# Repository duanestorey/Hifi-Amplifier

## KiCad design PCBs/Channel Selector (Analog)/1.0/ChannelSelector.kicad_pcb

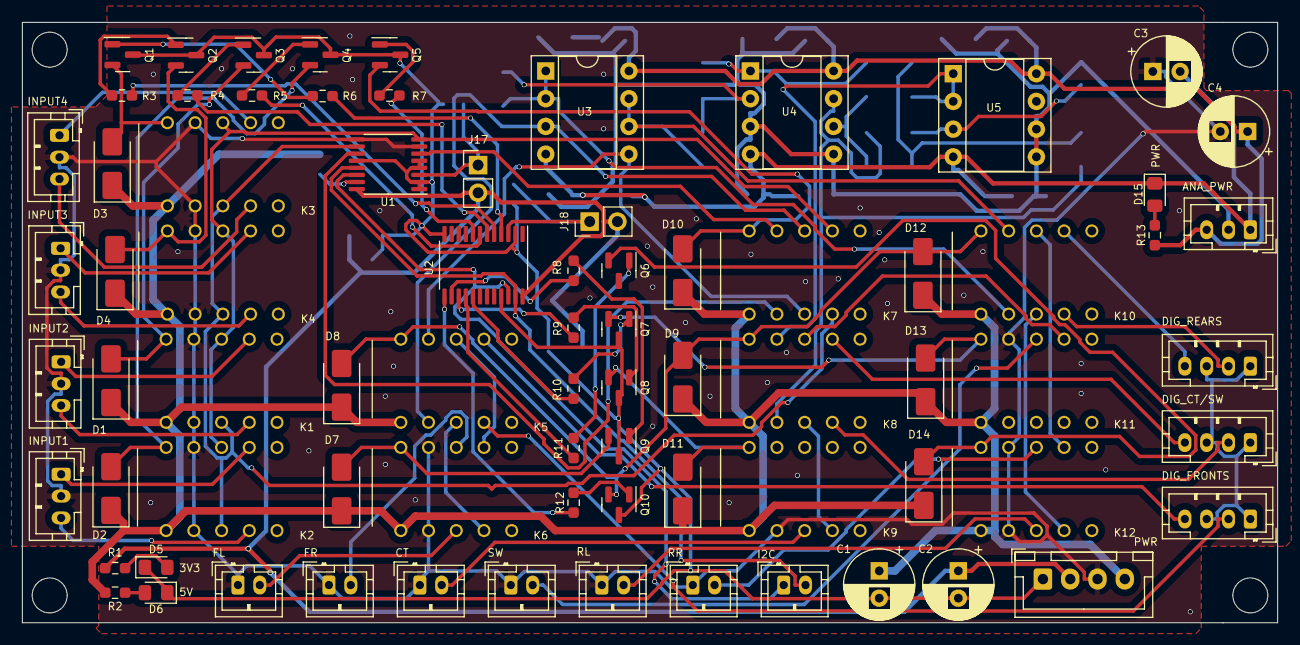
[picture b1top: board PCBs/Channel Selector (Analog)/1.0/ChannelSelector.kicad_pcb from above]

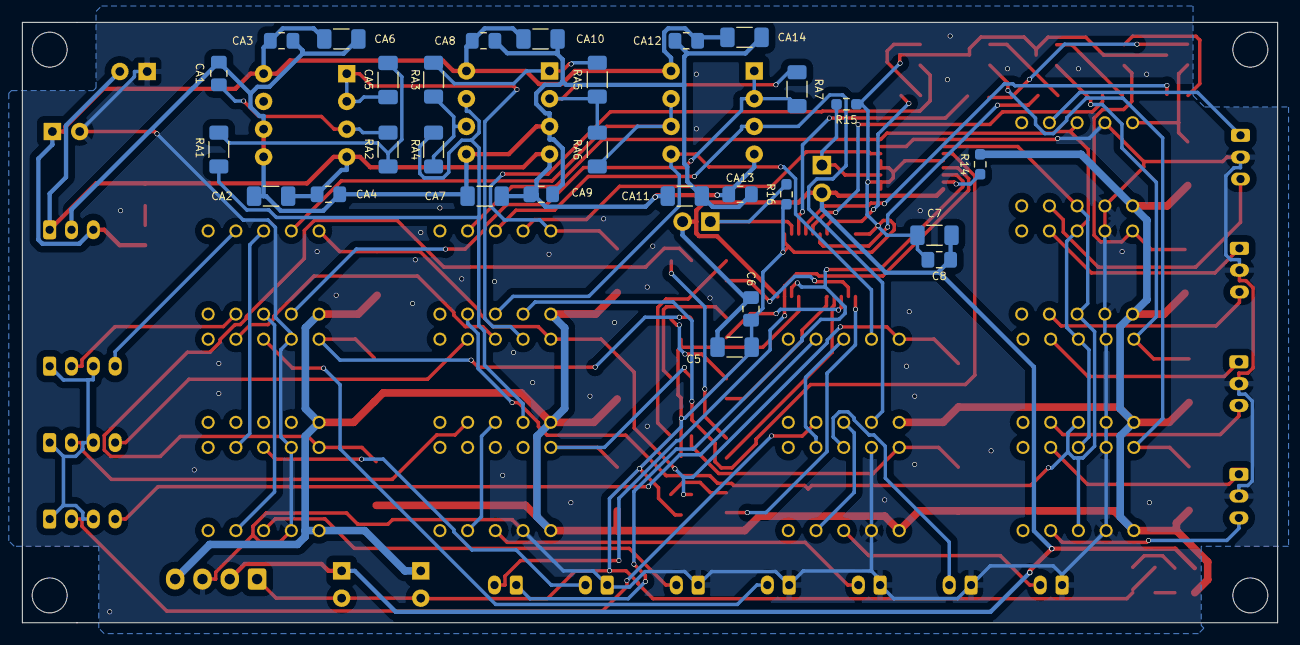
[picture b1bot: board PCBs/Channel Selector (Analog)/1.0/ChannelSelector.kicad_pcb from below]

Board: 2 copper layers, 115.0 x 55.0 mm, 109 parts (28 on the bottom side), 87 nets.

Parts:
C1, C2, C3, C4: 100u; CP_Radial_D6.3mm_P2.50mm
C5, C7: 10U; C_1206_3216Metric_Pad1.33x1.80mm_HandSolder
C6, C8: 0.1U; C_0805_2012Metric_Pad1.18x1.45mm_HandSolder
CA1: 10n; C_0805_2012Metric_Pad1.18x1.45mm_HandSolder
CA2, CA6, CA7, CA10, CA11, CA14: 10u; C_1206_3216Metric_Pad1.33x1.80mm_HandSolder
CA3, CA4, CA8, CA9, CA12, CA13: 0.1u; C_0805_2012Metric_Pad1.18x1.45mm_HandSolder
CA5: 100n; C_1206_3216Metric_Pad1.33x1.80mm_HandSolder
D1, D2, D3, D4, D7, D8, D9, D10, D11, D12, D13, D14: 1N4001; D_SMA
D5: YELLOW; LED_0805_2012Metric_Pad1.15x1.40mm_HandSolder
D6: BLUE; LED_0805_2012Metric_Pad1.15x1.40mm_HandSolder
D15: WHITE; LED_0805_2012Metric_Pad1.15x1.40mm_HandSolder
H1, H2, H3, H4: MountingHole; MountingHole_3.2mm_M3
J1, J2, J3, J4, J16: Conn_01x03_Pin; JST_PH_B3B-PH-K_1x03_P2.00mm_Vertical
J5, J6, J7, J8, J9, J10: Conn_01x02_Pin; JST_PH_B2B-PH-K_1x02_P2.00mm_Vertical
J11: Conn_01x02_Male; JST_PH_B2B-PH-K_1x02_P2.00mm_Vertical
J12: Conn_01x04_Pin; JST_XH_B4B-XH-A_1x04_P2.50mm_Vertical
J13, J14, J15: Conn_01x04_Pin; JST_PH_B4B-PH-K_1x04_P2.00mm_Vertical
J17, J18: Conn_01x02_Pin; PinHeader_1x02_P2.54mm_Vertical
K1, K3, K4, K5, K6, K7, K8, K9, K10, K11, K12: EC2-5NU; KEMET EA2
K2: KEMET; KEMET EA2
Q1, Q2, Q3, Q4, Q5, Q6, Q7, Q8, Q9, Q10: BC859; SOT-23
R1: 430R; R_0603_1608Metric_Pad0.98x0.95mm_HandSolder
R2, R15, R16: 670R; R_0603_1608Metric_Pad0.98x0.95mm_HandSolder
R3, R4, R5, R6, R7, R8, R9, R10, R11, R12: 1K; R_0603_1608Metric_Pad0.98x0.95mm_HandSolder
R13: 5K; R_0603_1608Metric_Pad0.98x0.95mm_HandSolder
R14: 0R; R_0603_1608Metric_Pad0.98x0.95mm_HandSolder
RA1: 7.5K; R_1206_3216Metric_Pad1.30x1.75mm_HandSolder
RA2: 130K; R_1206_3216Metric_Pad1.30x1.75mm_HandSolder
RA3, RA4, RA5: 1K; R_1206_3216Metric_Pad1.30x1.75mm_HandSolder
RA6, RA7: 2K; R_1206_3216Metric_Pad1.30x1.75mm_HandSolder
U1: DS1881; TSSOP-16_4.4x5mm_P0.65mm
U2: TCA9555; TSSOP-24_4.4x7.8mm_P0.65mm
U3, U4, U5: OPA2134; DIP-8_W7.62mm_Socket

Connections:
3V3: C2.1, C5.1, C6.1, C7.1, C8.1, J12.2, J17.2, J18.2, R1.1, U1.16 (VDD), U2.24 (VDD)
5CHGND: J13.1, J13.3, J14.1, J14.3, J15.1, J15.3
5V: C1.1, D1.1 (K), D2.1 (K), D3.1 (K), D4.1 (K), D7.1 (K), D8.1 (K), D9.1 (K), D10.1 (K), D11.1 (K), D12.1 (K), D13.1 (K), D14.1 (K), J12.4, K1.1, K2.1, K3.1, K4.1, K5.1, K6.1, K7.1, K8.1, K9.1, K10.1, K11.1, K12.1, R2.1, R14.2
AGND: C3.1, C4.2, J1.2, J2.2, J3.2, J4.2, J5.1, J6.1, J7.1, J8.1, J9.1, J10.1, J12.3, K1.3, K1.10, K2.3, K2.10, K3.3, K3.10, K4.3, K4.10, K6.3, K6.10, K9.3, K11.10, K12.3, K12.10, U1.7 (L0), U1.9 (L1)
CT: J7.2, K9.4
CT_A: K8.3, RA1.1, RA4.1, U4.7 (OutB)
CT_DIG: J14.2, K8.5
CT_EN: R9.1, U2.15 (IO1_2)
CT_SIG: K8.4, K9.5
DIGCTL: R12.1, U2.13 (IO1_0)
FL: J5.2, K6.4
FL_A: K5.3, K7.9, U3.3 (InA+)
FL_AIN: K1.9, K2.9, K3.9, K4.9, K7.8, U1.8 (H0)
FL_AV: K7.10, U1.6 (W0)
FL_DIG: J15.2, K5.5
FL_SIG: K5.4, K6.5
FR: J6.2, K6.9
FRONT_EN: R8.1, U2.14 (IO1_1)
FR_A: K5.10, K7.4, U3.5 (InB+)
FR_AIN: K1.4, K2.4, K3.4, K4.4, K7.5, U1.10 (H1)
FR_AV: K7.3, U1.11 (W1)
FR_DIG: J15.4, K5.8
FR_SIG: K5.9, K6.8
GND: C1.2, C2.2, C5.2, C6.2, C7.2, C8.2, D5.1 (K), D6.1 (K), J12.1, Q1.3 (C), Q2.3 (C), Q3.3 (C), Q4.3 (C), Q5.3 (C), Q7.3 (C), Q8.3 (C), Q9.3 (C), Q10.3 (C), R15.1, R16.1, U1.1 (GND), U1.2 (A2), U1.4 (V-), U1.5 (A0), U1.12 (~CE), U2.2 (A1), U2.12 (VSS), U2.21 (A0)
GPIO_A2: J18.1, R16.2, U2.3 (A2)
unnamed: CA5.2, RA1.2, RA2.1
unnamed: D1.2 (A), K1.12, Q3.2 (E)
unnamed: D2.2 (A), K2.12, Q4.2 (E)
unnamed: D3.2 (A), K3.12, Q1.2 (E)
unnamed: D4.2 (A), K4.12, Q2.2 (E)
unnamed: D5.2 (A), R1.2
unnamed: D6.2 (A), R2.2
unnamed: D7.2 (A), K6.12, Q9.2 (E)
unnamed: D10.2 (A), K7.12, Q5.2 (E)
unnamed: D11.2 (A), K9.12, Q8.2 (E)
unnamed: D8.2 (A), D9.2 (A), D12.2 (A), K5.12, K8.12, K10.12, Q10.2 (E)
unnamed: D13.2 (A), K11.12, Q7.2 (E)
unnamed: D14.2 (A), K12.12, Q6.2 (E)
unnamed: D15.2 (A), R13.2
unnamed: Q1.1 (B), R6.2
unnamed: Q2.1 (B), R3.2
unnamed: Q3.1 (B), R4.2
unnamed: Q4.1 (B), R5.2
unnamed: Q5.1 (B), R7.2
unnamed: Q6.1 (B), R11.2
unnamed: Q7.1 (B), R10.2
unnamed: Q8.1 (B), R9.2
unnamed: Q9.1 (B), R8.2
unnamed: Q10.1 (B), R12.2
unnamed: R14.1, U1.15 (VCC)
unnamed: RA5.1, RA6.2, RA7.2, U4.2 (InA-)
unnamed: RA3.1, RA4.2, U4.6 (InB-)
unnamed: RA3.2, RA5.2, U4.1 (OutA)
unnamed: CA1.2, RA2.2, U5.3 (InA+)
OPGND: CA1.1, CA2.1, CA3.1, CA4.1, CA6.1, CA7.1, CA8.1, CA9.1, CA10.1, CA11.1, CA12.1, CA13.1, CA14.1, J16.2, U4.3 (InA+), U4.5 (InB+), U5.5 (InB+), U5.6 (InB-)
POT_A1: J17.1, R15.2, U1.3 (A1)
RCA1: R5.1, U2.7 (IO0_3)
RCA1_L: J4.1, K2.8
RCA1_R: J4.3, K2.5
RCA2: R4.1, U2.6 (IO0_2)
RCA2_L: J3.1, K1.8
RCA2_R: J3.3, K1.5
RCA3: R3.1, U2.5 (IO0_1)
RCA3_L: J2.1, K4.8
RCA3_R: J2.3, K4.5
RCA4: R6.1, U2.4 (IO0_0)
RCA4_L: J1.1, K3.8
RCA4_R: J1.3, K3.5
REARS_EN: R11.1, U2.16 (IO1_3)
RL: J9.2, K12.4
RL_A: K10.3, RA7.1, U3.1 (OutA), U3.2 (InA-)
RL_DIG: J13.2, K10.5
RL_SIG: K10.4, K12.5
RR: J10.2, K12.9
RR_A: K10.10, RA6.1, U3.6 (InB-), U3.7 (OutB)
RR_DIG: J13.4, K10.8
RR_SIG: K10.9, K12.8
SCL: J11.1, U1.14 (SCL), U2.22 (SCL)
SDA: J11.2, U1.13 (SDA), U2.23 (SDA)
SW: J8.2, K11.9
SW_A: CA5.1, K8.10, U5.1 (OutA), U5.2 (InA-)
SW_DIG: J14.4, K8.8
SW_EN: R10.1, U2.17 (IO1_4)
SW_SIG: K8.9, K11.8
V+: C4.1, CA3.2, CA6.2, CA8.2, CA10.2, CA12.2, CA14.2, J16.3, R13.1, U3.8 (V+), U4.8 (V+), U5.8 (V+)
V-: C3.2, CA2.2, CA4.2, CA7.2, CA9.2, CA11.2, CA13.2, D15.1 (K), J16.1, U3.4 (V-), U4.4 (V-), U5.4 (V-)
VOLCTL: R7.1, U2.8 (IO0_4)

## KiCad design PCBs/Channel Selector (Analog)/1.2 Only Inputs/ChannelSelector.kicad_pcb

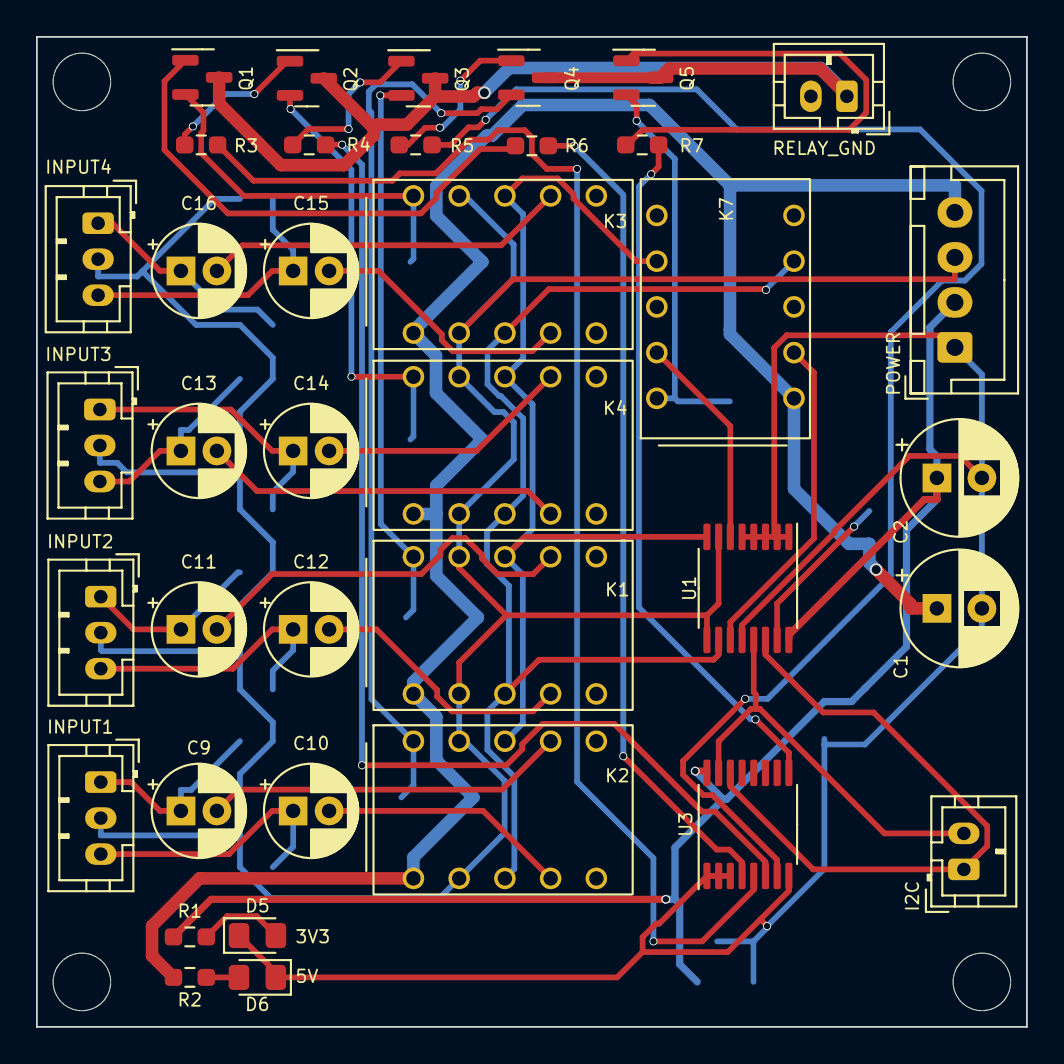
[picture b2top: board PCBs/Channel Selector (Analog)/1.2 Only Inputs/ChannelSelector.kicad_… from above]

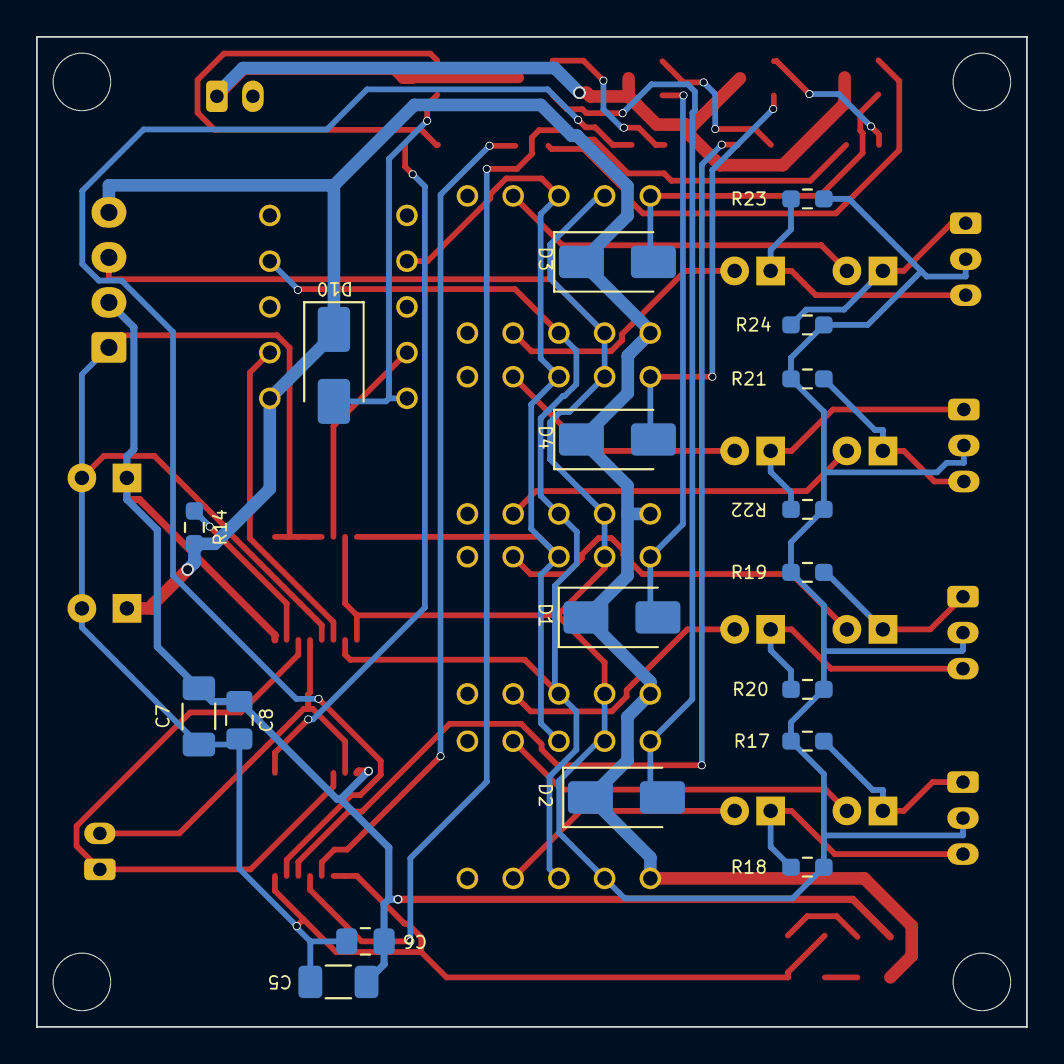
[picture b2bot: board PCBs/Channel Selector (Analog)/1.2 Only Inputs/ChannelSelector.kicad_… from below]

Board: 2 copper layers, 55.0 x 55.0 mm, 60 parts (18 on the bottom side), 45 nets.

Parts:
C1, C2: 100u; CP_Radial_D6.3mm_P2.50mm
C5, C7: 10U; C_1206_3216Metric_Pad1.33x1.80mm_HandSolder
C6, C8: 0.1U; C_0805_2012Metric_Pad1.18x1.45mm_HandSolder
C9, C10, C11, C12, C13, C14, C15, C16: 10u; CP_Radial_D5.0mm_P2.00mm
D1, D2, D3, D4, D10: 1N4001; D_SMA
D5: YELLOW; LED_0805_2012Metric_Pad1.15x1.40mm_HandSolder
D6: BLUE; LED_0805_2012Metric_Pad1.15x1.40mm_HandSolder
H1, H2, H3, H4: MountingHole; MountingHole_3.2mm_M3
J1, J2, J3, J4: Conn_01x03_Pin; JST_PH_B3B-PH-K_1x03_P2.00mm_Vertical
J11: Conn_01x02_Male; JST_PH_B2B-PH-K_1x02_P2.00mm_Vertical
J12: Conn_01x04_Pin; JST_XH_B4B-XH-A_1x04_P2.50mm_Vertical
J19: Conn_01x02_Pin; JST_PH_B2B-PH-K_1x02_P2.00mm_Vertical
K1, K3, K4, K7: EC2-5NU; KEMET EA2
K2: KEMET; KEMET EA2
Q1, Q2, Q3, Q4, Q5: BC859; SOT-23
R1: 430R; R_0603_1608Metric_Pad0.98x0.95mm_HandSolder
R2: 670R; R_0603_1608Metric_Pad0.98x0.95mm_HandSolder
R3, R4, R5, R6, R7: 1K; R_0603_1608Metric_Pad0.98x0.95mm_HandSolder
R14: 0R; R_0603_1608Metric_Pad0.98x0.95mm_HandSolder
R17, R18, R19, R20, R21, R22, R23, R24: 10K; R_0603_1608Metric_Pad0.98x0.95mm_HandSolder
U1: DS1881; TSSOP-16_4.4x5mm_P0.65mm
U3: TCA9554PW; TSSOP-16_4.4x5mm_P0.65mm

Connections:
3V3: C2.1, C5.1, C6.1, C7.1, C8.1, J12.2, R1.1, U1.16 (VDD), U3.16 (VDD)
5V: C1.1, D1.1 (K), D2.1 (K), D3.1 (K), D4.1 (K), D10.1 (K), J12.4, K1.1, K2.1, K3.1, K4.1, K7.1, R2.1, R14.2
AGND: J1.2, J2.2, J3.2, J4.2, J12.3, K1.3, K1.10, K2.3, K2.10, K3.3, K3.10, K4.3, K4.10, R17.1, R18.1, R19.1, R20.1, R21.1, R22.1, R23.1, R24.1, U1.7 (L0), U1.9 (L1)
FL_AIN: K1.9, K2.9, K3.9, K4.9, K7.8, U1.8 (H0)
FL_AV: K7.10, U1.6 (W0)
FR_AIN: K1.4, K2.4, K3.4, K4.4, K7.5, U1.10 (H1)
FR_AV: K7.3, U1.11 (W1)
GND: C1.2, C2.2, C5.2, C6.2, C7.2, C8.2, D5.1 (K), D6.1 (K), J12.1, U1.1 (GND), U1.2 (A2), U1.3 (A1), U1.4 (V-), U1.5 (A0), U1.12 (~CE), U3.1 (A0), U3.2 (A1), U3.3 (A2), U3.8 (GND)
unnamed: D1.2 (A), K1.12, Q3.2 (E)
unnamed: D2.2 (A), K2.12, Q4.2 (E)
unnamed: D3.2 (A), K3.12, Q1.2 (E)
unnamed: D4.2 (A), K4.12, Q2.2 (E)
unnamed: D5.2 (A), R1.2
unnamed: D6.2 (A), R2.2
unnamed: D10.2 (A), K7.12, Q5.2 (E)
unnamed: C16.1, J1.1, R24.2
unnamed: C15.1, J1.3, R23.2
unnamed: C14.1, J2.1, R22.2
unnamed: C13.1, J2.3, R21.2
unnamed: C11.1, J3.1, R19.2
unnamed: C12.1, J3.3, R20.2
unnamed: C9.1, J4.1, R17.2
unnamed: C10.1, J4.3, R18.2
unnamed: Q1.1 (B), R6.2
unnamed: Q2.1 (B), R3.2
unnamed: Q3.1 (B), R4.2
unnamed: Q4.1 (B), R5.2
unnamed: Q5.1 (B), R7.2
unnamed: R14.1, U1.15 (VCC)
PGND: J19.1, Q1.3 (C), Q2.3 (C), Q3.3 (C), Q4.3 (C), Q5.3 (C)
RCA1: R5.1, U3.7 (P3)
RCA1_L: C9.2, K2.8
RCA1_R: C10.2, K2.5
RCA2: R4.1, U3.6 (P2)
RCA2_L: C11.2, K1.8
RCA2_R: C12.2, K1.5
RCA3: R3.1, U3.5 (P1)
RCA3_L: C14.2, K4.8
RCA3_R: C13.2, K4.5
RCA4: R6.1, U3.4 (P0)
RCA4_L: C16.2, K3.8
RCA4_R: C15.2, K3.5
SCL: J11.1, U1.14 (SCL), U3.14 (SCL)
SDA: J11.2, U1.13 (SDA), U3.15 (SDA)
VOLCTL: R7.1, U3.9 (P4)

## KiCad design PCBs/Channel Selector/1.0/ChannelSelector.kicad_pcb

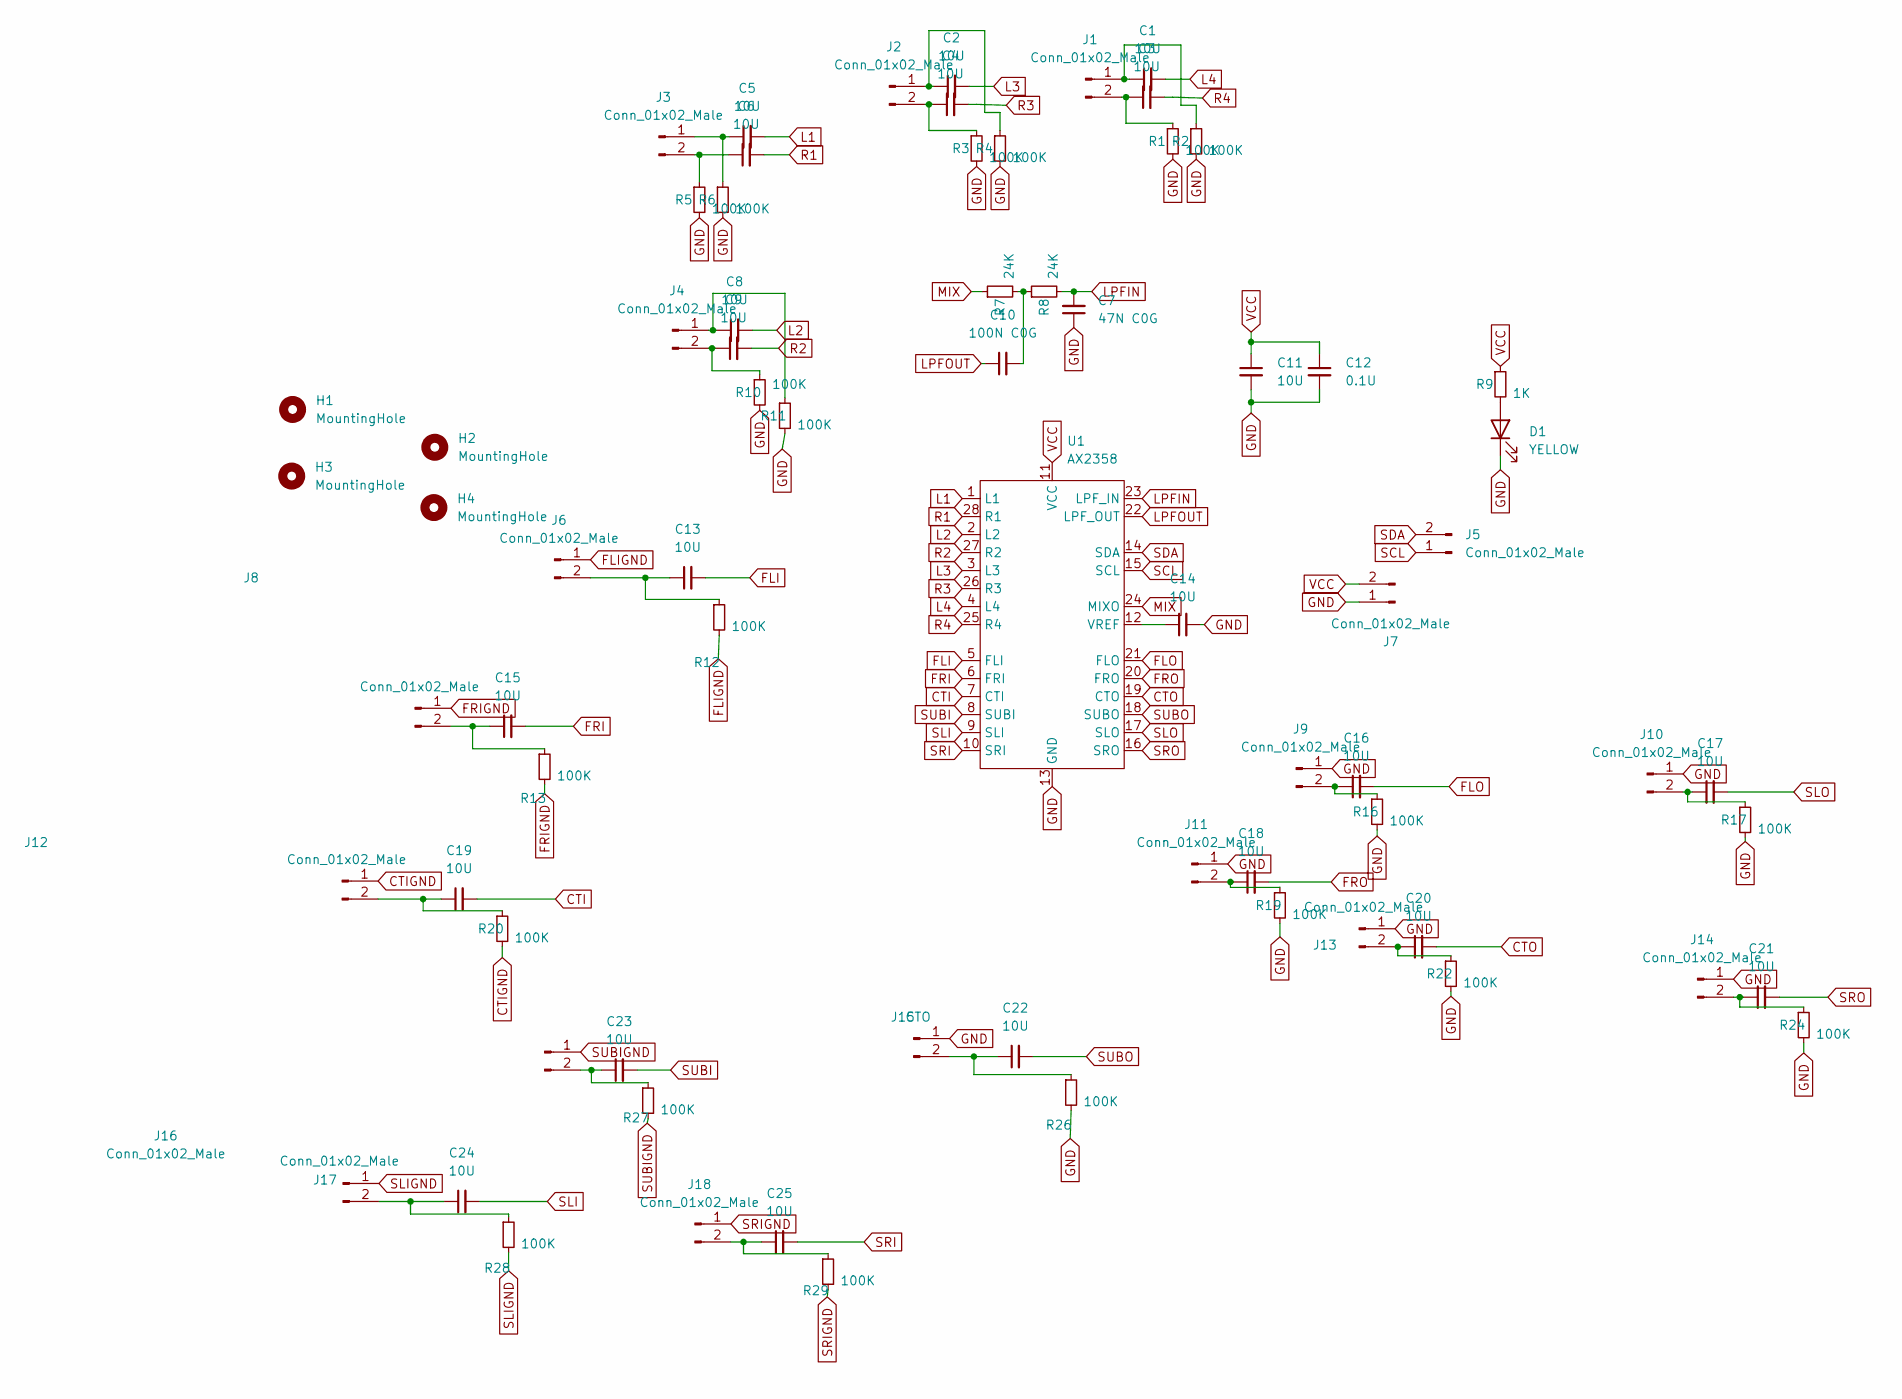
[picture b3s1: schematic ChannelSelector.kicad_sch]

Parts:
C1, C2, C3, C4, C5, C6, C8, C9, C13, C15, C16, C17, C18, C19, C20, C21, C22, C23, C24, C25: 10U; CP_Radial_D5.0mm_P2.50mm
C7: 47N C0G; C_1206_3216Metric_Pad1.33x1.80mm_HandSolder
C10: 100N C0G; C_1206_3216Metric_Pad1.33x1.80mm_HandSolder
C11, C14: 10U; C_1206_3216Metric_Pad1.33x1.80mm_HandSolder
C12: 0.1U; C_0805_2012Metric_Pad1.18x1.45mm_HandSolder
D1: YELLOW; LED_0805_2012Metric_Pad1.15x1.40mm_HandSolder
H1, H2, H3, H4: MountingHole; MountingHole_3.2mm_M3
J1, J2, J3, J4, J5, J6, J7, J8, J9, J10, J11, J12, J13, J14, J16, J17, J18: Conn_01x02_Male; JST_PH_B2B-PH-K_1x02_P2.00mm_Vertical
J15: CTO; JST_PH_B2B-PH-K_1x02_P2.00mm_Vertical
R1, R2, R3, R4, R5, R6, R10, R11, R12, R13, R16, R17, R19, R20, R22, R24, R26, R27, R28, R29: 100K; R_0805_2012Metric_Pad1.20x1.40mm_HandSolder
R7, R8: 24K; R_0805_2012Metric_Pad1.20x1.40mm_HandSolder
R9: 1K; R_0603_1608Metric_Pad0.98x0.95mm_HandSolder
U1: AX2358; SOIC-28W_7.5x18.7mm_P1.27mm

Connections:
CTI: C19.2, U1.7 (CTI)
CTIGND: J12.1, R20.2
CTO: C20.2, U1.19 (CTO)
FLI: C13.2, U1.5 (FLI)
FLIGND: J6.1, R12.2
FLO: C16.2, U1.21 (FLO)
FRI: C15.2, U1.6 (FRI)
FRIGND: J8.1, R13.2
FRO: C18.2, U1.20 (FRO)
GND: C7.1, C11.2, C12.2, C14.2, D1.1 (K), J7.1, J9.1, J10.1, J11.1, J13.1, J14.1, J15.1, R1.2, R2.2, R3.2, R4.2, R5.2, R6.2, R10.2, R11.2, R16.2, R17.2, R19.2, R22.2, R24.2, R26.2, U1.13 (GND)
L1: C5.2, U1.1 (L1)
L2: C8.2, U1.2 (L2)
L3: C2.2, U1.3 (L3)
L4: C1.2, U1.4 (L4)
LPFIN: C7.2, R8.2, U1.23 (LPF_IN)
LPFOUT: C10.1, U1.22 (LPF_OUT)
MIX: R7.1, U1.24 (MIXO)
unnamed: C10.2, R7.2, R8.1
unnamed: D1.2 (A), R9.2
unnamed: C1.1, J1.1, R2.1
unnamed: C3.1, J1.2, R1.1
unnamed: C2.1, J2.1, R4.1
unnamed: C4.1, J2.2, R3.1
unnamed: C5.1, J3.1, R6.1
unnamed: C6.1, J3.2, R5.1
unnamed: C8.1, J4.1, R11.1
unnamed: C9.1, J4.2, R10.1
unnamed: C13.1, J6.2, R12.1
unnamed: C15.1, J8.2, R13.1
unnamed: C16.1, J9.2, R16.1
unnamed: C17.1, J10.2, R17.1
unnamed: C18.1, J11.2, R19.1
unnamed: C19.1, J12.2, R20.1
unnamed: C20.1, J13.2, R22.1
unnamed: C21.1, J14.2, R24.1
unnamed: C22.1, J15.2, R26.1
unnamed: C23.1, J16.2, R27.1
unnamed: C24.1, J17.2, R28.1
unnamed: C25.1, J18.2, R29.1
unnamed: C14.1, U1.12 (VREF)
R1: C6.2, U1.28 (R1)
R2: C9.2, U1.27 (R2)
R3: C4.2, U1.26 (R3)
R4: C3.2, U1.25 (R4)
SCL: J5.1, U1.15 (SCL)
SDA: J5.2, U1.14 (SDA)
SLI: C24.2, U1.9 (SLI)
SLIGND: J17.1, R28.2
SLO: C17.2, U1.17 (SLO)
SRI: C25.2, U1.10 (SRI)
SRIGND: J18.1, R29.2
SRO: C21.2, U1.16 (SRO)
SUBI: C23.2, U1.8 (SUBI)
SUBIGND: J16.1, R27.2
SUBO: C22.2, U1.18 (SUBO)
VCC: C11.1, C12.1, J7.2, R9.1, U1.11 (VCC)

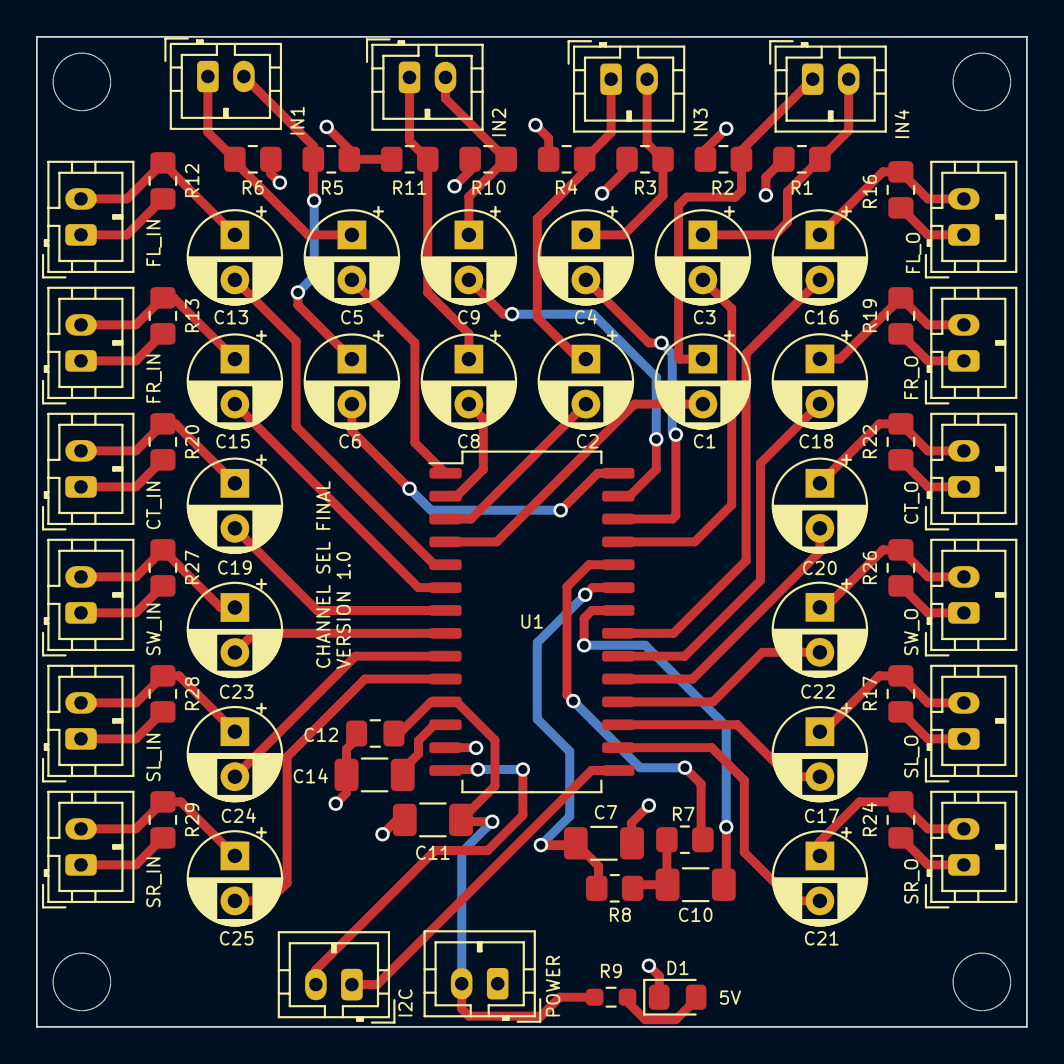
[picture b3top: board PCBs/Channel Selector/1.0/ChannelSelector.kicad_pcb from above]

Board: 2 copper layers, 55.0 x 55.0 mm, 72 parts (0 on the bottom side), 56 nets.

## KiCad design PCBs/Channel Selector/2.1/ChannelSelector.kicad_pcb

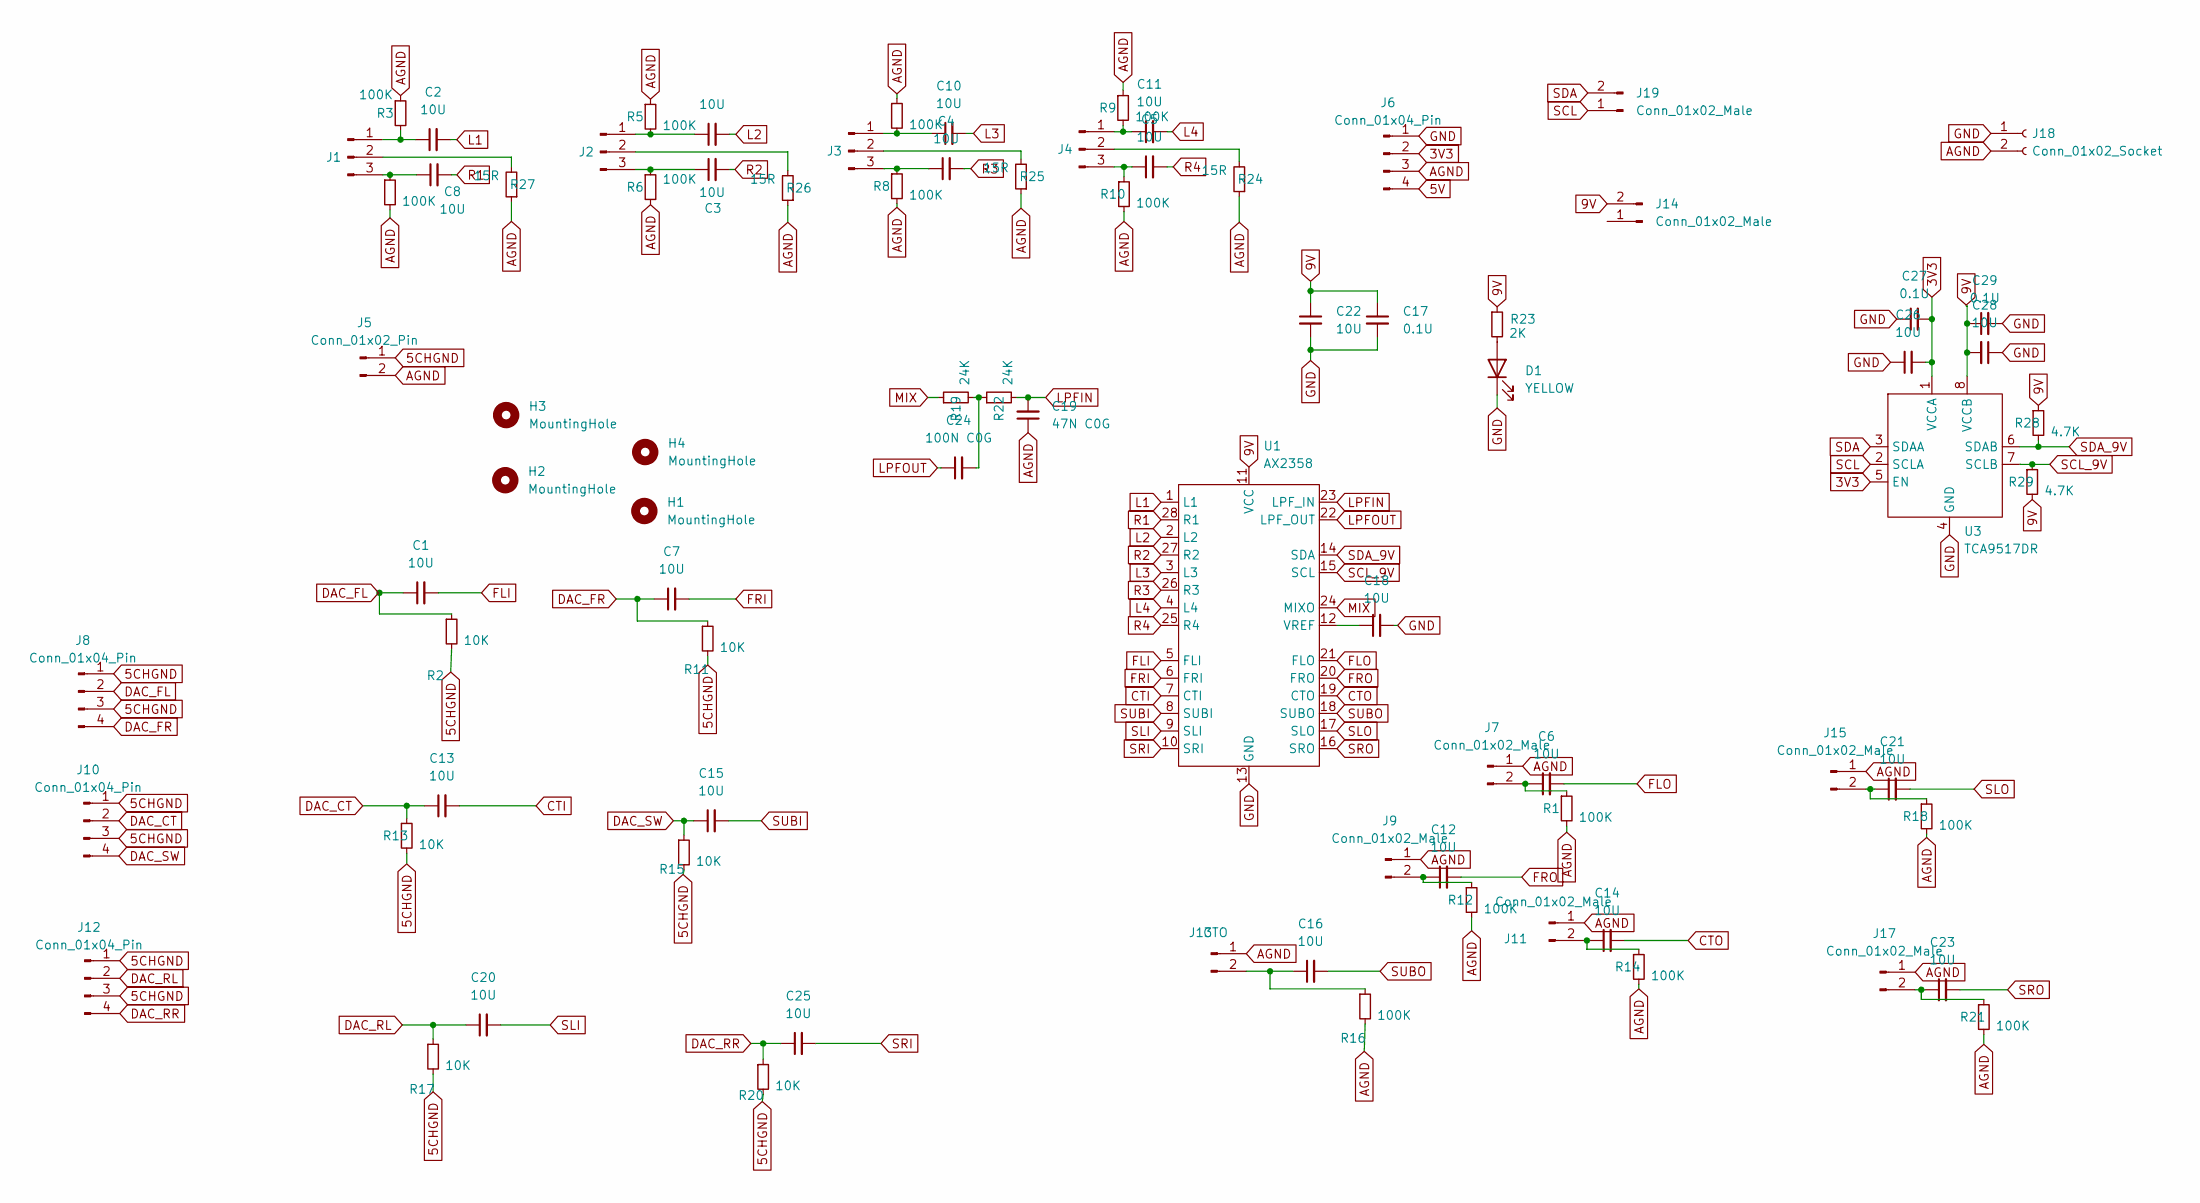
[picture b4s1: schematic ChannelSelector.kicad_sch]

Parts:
C1, C2, C3, C4, C5, C6, C7, C8, C9, C10, C11, C12, C13, C14, C15, C16, C20, C21, C23, C25: 10U; CP_Radial_D5.0mm_P2.50mm
C17, C27, C29: 0.1U; C_0805_2012Metric_Pad1.18x1.45mm_HandSolder
C18, C22, C26, C28: 10U; C_1206_3216Metric_Pad1.33x1.80mm_HandSolder
C19: 47N C0G; C_1206_3216Metric_Pad1.33x1.80mm_HandSolder
C24: 100N C0G; C_1206_3216Metric_Pad1.33x1.80mm_HandSolder
D1: YELLOW; LED_0805_2012Metric_Pad1.15x1.40mm_HandSolder
H1, H2, H3, H4: MountingHole; MountingHole_3.2mm_M3
J1, J2, J3, J4: Conn_01x03_Pin; JST_PH_B3B-PH-K_1x03_P2.00mm_Vertical
J5: Conn_01x02_Pin; PinHeader_1x02_P2.54mm_Vertical
J6: Conn_01x04_Pin; JST_XH_B4B-XH-A_1x04_P2.50mm_Vertical
J7, J9, J11, J14, J15, J17, J19: Conn_01x02_Male; JST_PH_B2B-PH-K_1x02_P2.00mm_Vertical
J8, J10, J12: Conn_01x04_Pin; JST_PH_B4B-PH-K_1x04_P2.00mm_Vertical
J13: CTO; JST_PH_B2B-PH-K_1x02_P2.00mm_Vertical
J18: Conn_01x02_Socket; PinHeader_1x02_P2.54mm_Vertical
R1, R3, R4, R5, R6, R7, R8, R9, R10, R12, R14, R16, R18, R21: 100K; R_0805_2012Metric_Pad1.20x1.40mm_HandSolder
R2, R11, R13, R15, R17, R20: 10K; R_0805_2012Metric_Pad1.20x1.40mm_HandSolder
R19, R22: 24K; R_0805_2012Metric_Pad1.20x1.40mm_HandSolder
R23: 2K; R_0603_1608Metric_Pad0.98x0.95mm_HandSolder
R24, R25, R26, R27: 15R; R_0603_1608Metric_Pad0.98x0.95mm_HandSolder
R28, R29: 4.7K; R_0603_1608Metric_Pad0.98x0.95mm_HandSolder
U1: AX2358; SOIC-28W_7.5x18.7mm_P1.27mm
U3: TCA9517DR; SOIC-8_3.9x4.9mm_P1.27mm

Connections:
3V3: C26.2, C27.2, J6.2; also elsewhere on the board
5CHGND: J5.1, J8.1, J8.3, J10.1, J10.3, J12.1, J12.3, R2.2, R11.2, R13.2, R15.2, R17.2, R20.2
5V: J6.4
9V: C17.1, C22.1, C28.2, C29.1, J14.2, R23.1, R28.1, R29.2, U1.11 (VCC); also elsewhere on the board
AGND: C19.1, J5.2, J6.3, J7.1, J9.1, J11.1, J13.1, J15.1, J17.1, J18.2, R1.2, R3.1, R4.2, R5.1, R6.2, R7.1, R8.2, R9.1, R10.2, R12.2, R14.2, R16.2, R18.2, R21.2, R24.1, R25.1, R26.1, R27.1
CTI: C13.2, U1.7 (CTI)
CTO: C14.2, U1.19 (CTO)
DAC_CT: C13.1, J10.2, R13.1
DAC_FL: C1.1, J8.2, R2.1
DAC_FR: C7.1, J8.4, R11.1
DAC_RL: C20.1, J12.2, R17.1
DAC_RR: C25.1, J12.4, R20.1
DAC_SW: C15.1, J10.4, R15.1
FLI: C1.2, U1.5 (FLI)
FLO: C6.2, U1.21 (FLO)
FRI: C7.2, U1.6 (FRI)
FRO: C12.2, U1.20 (FRO)
GND: C17.2, C18.2, C22.2, C26.1, C27.1, C28.1, C29.2, D1.1 (K), J6.1, J18.1, U1.13 (GND); also elsewhere on the board
L1: C2.2, U1.1 (L1)
L2: C9.2, U1.2 (L2)
L3: C10.2, U1.3 (L3)
L4: C11.2, U1.4 (L4)
LPFIN: C19.2, R22.2, U1.23 (LPF_IN)
LPFOUT: C24.1, U1.22 (LPF_OUT)
MIX: R19.1, U1.24 (MIXO)
unnamed: C24.2, R19.2, R22.1
unnamed: D1.2 (A), R23.2
unnamed: C2.1, J1.1, R3.2
unnamed: J1.2, R27.2
unnamed: C8.1, J1.3, R4.1
unnamed: C9.1, J2.1, R5.2
unnamed: J2.2, R26.2
unnamed: C3.1, J2.3, R6.1
unnamed: C10.1, J3.1, R7.2
unnamed: J3.2, R25.2
unnamed: C4.1, J3.3, R8.1
unnamed: C11.1, J4.1, R9.2
unnamed: J4.2, R24.2
unnamed: C5.1, J4.3, R10.1
unnamed: C6.1, J7.2, R1.1
unnamed: C12.1, J9.2, R12.1
unnamed: C14.1, J11.2, R14.1
unnamed: C16.1, J13.2, R16.1
unnamed: C21.1, J15.2, R18.1
unnamed: C23.1, J17.2, R21.1
unnamed: C18.1, U1.12 (VREF)
R1: C8.2, U1.28 (R1)
R2: C3.2, U1.27 (R2)
R3: C4.2, U1.26 (R3)
R4: C5.2, U1.25 (R4)
SCL: J19.1; also elsewhere on the board
SCL_9V: R29.1, U1.15 (SCL); also elsewhere on the board
SDA: J19.2; also elsewhere on the board
SDA_9V: R28.2, U1.14 (SDA); also elsewhere on the board
SLI: C20.2, U1.9 (SLI)
SLO: C21.2, U1.17 (SLO)
SRI: C25.2, U1.10 (SRI)
SRO: C23.2, U1.16 (SRO)
SUBI: C15.2, U1.8 (SUBI)
SUBO: C16.2, U1.18 (SUBO)

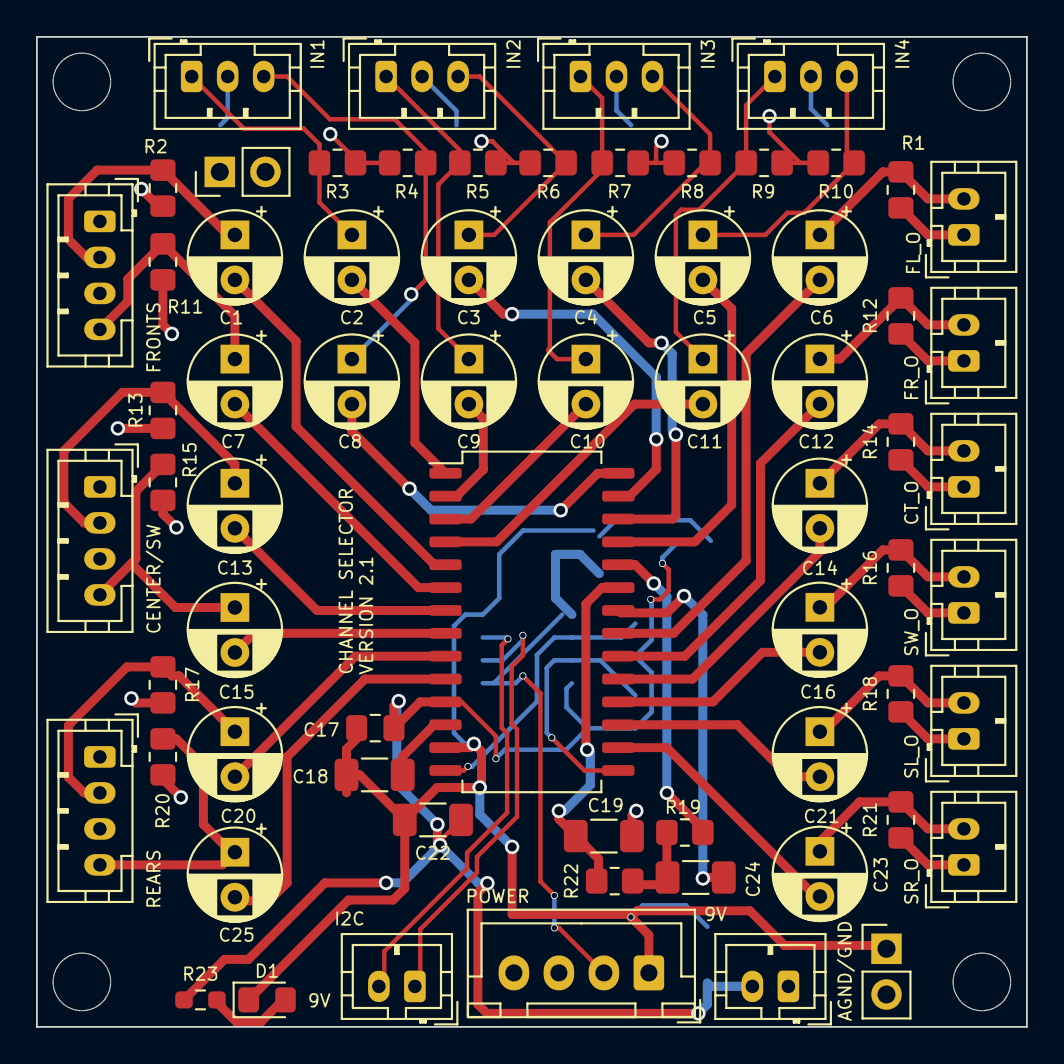
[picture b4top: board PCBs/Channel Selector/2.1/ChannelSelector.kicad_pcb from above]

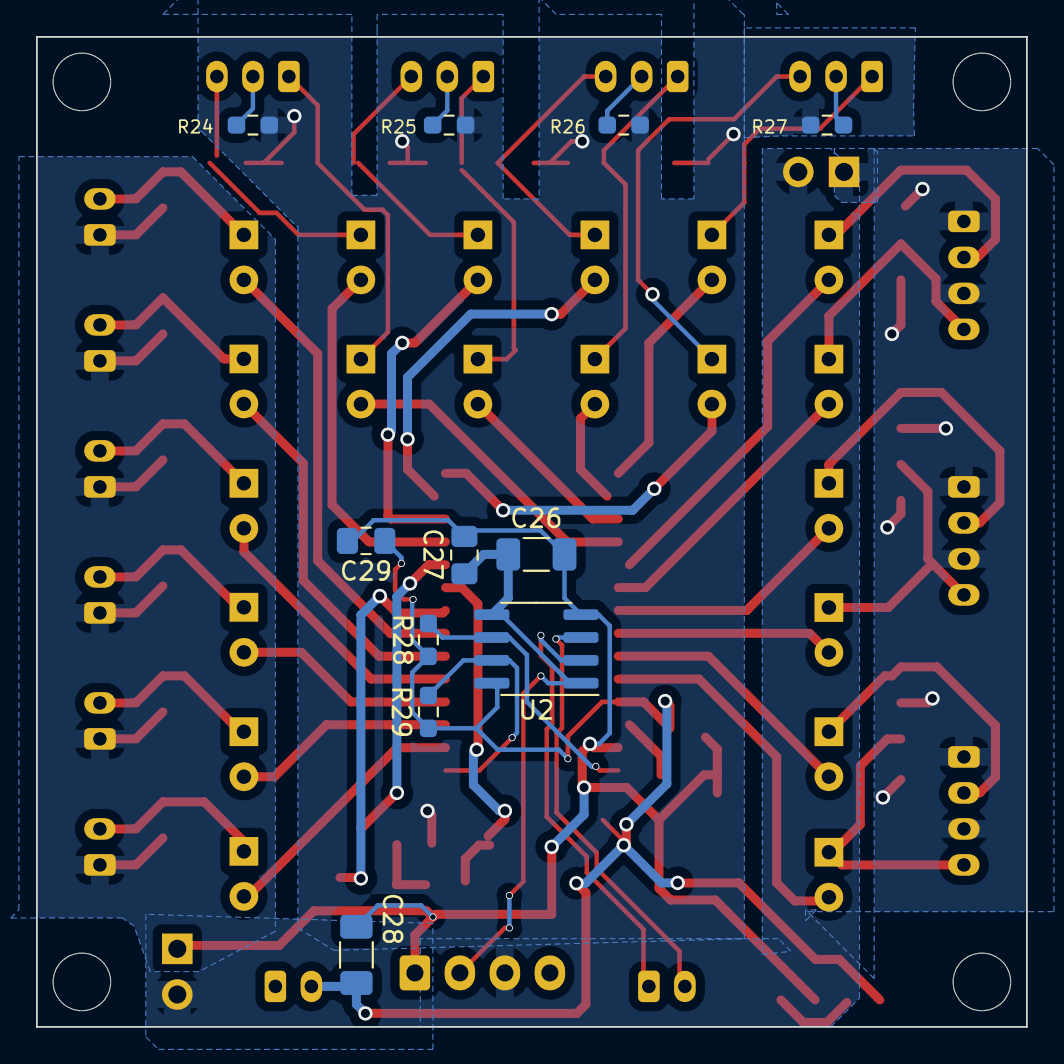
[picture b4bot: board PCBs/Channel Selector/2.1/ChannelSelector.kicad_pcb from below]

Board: 2 copper layers, 55.0 x 55.0 mm, 83 parts (11 on the bottom side), 59 nets.

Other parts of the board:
U2: TCA9517DR; SOIC-8_3.9x4.9mm_P1.27mm

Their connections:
3V3: U2.1 (VCCA), U2.5 (EN); also elsewhere on the board
9V: U2.8 (VCCB); also elsewhere on the board
GND: U2.4 (GND); also elsewhere on the board
SCL: U2.2 (SCLA); also elsewhere on the board
SCL_9V: U2.7 (SCLB); also elsewhere on the board
SDA: U2.3 (SDAA); also elsewhere on the board
SDA_9V: U2.6 (SDAB); also elsewhere on the board
